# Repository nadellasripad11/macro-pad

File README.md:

# macro pad

a small macro pad i designed for week 5 freestyle. looks only, it is a
display model, it just has to look good on a desk.

## the idea

i wanted to make something clean that looks good on my desk every day.

so i started designing a macro pad with 12 keys and a scroll wheel on
the side. no screen, no rgb, no wiring, just something clean that looks
good. the look is minimal black and silver.

## what i am building

* 12 keys arranged in a 3x4 grid
* a silver metal mouse scroll wheel in a slot on the right edge, about
  half of it sticking out past the edge, like a mouse wheel
* black keycaps with little grey line icons instead of words
* a silver aluminum plate
* no board, no pcb, no wiring, no firmware, it does not work as a
  keyboard

the keycaps are relegendable, i print the line icons and slide them
under the clear tops. the switches just clip into the plate and hold
the keycaps, no soldering. the wheel is a real 25 mm mouse wheel, the
little encoder behind it only holds its axle, it is not wired to
anything.

## the hardware

the plate is custom cut aluminum, 112 by 70 mm, from md cnc. the
switches are gateron milky pro yellow, they clip into the plate and
hold the keycaps. the wheel is a metal mouse scroll wheel, about 25 mm,
for a logitech g102/g304/g305, and the encoder under it is a ttc 11 mm
mouse wheel encoder, mount only.

here are some of the main dimensions:

component	dimensions
plate	112 x 70 mm
key layout	3 x 4
key spacing	19.05 mm
key cutouts	14 x 14 mm
wheel slot	25 mm long plus clearance, width is the wheel thickness
plus about 1 mm, measure the wheel with calipers on arrival first

the dxf still has the old 7 mm round knob hole in it, the slot goes in
once the wheel is measured.

## the design files

everything is organized in the repository so the design can be reviewed
and worked on separately.

* plate/ contains the plate dxf
* images/ contains design and plate images
* cart-screenshots/ contains parts and quote screenshots

the pcb/ and firmware/ files still in this repo are from the earlier
functional plan and are not part of this build. the gerbers were not
plotted in kicad, they were generated in python, do not order from
them. there are also pin mappings, a netlist, and a draft bill of
materials from that earlier plan, also not part of this build.

## parts and costs

tier 1, total $28.77 at regular prices, verified live november 8. cap
is $33, headroom $4.23. all five lines ship free.

part	price
md cnc custom plate, aluminum, 112x70	$7.15
gateron milky pro yellow switches, 2x 10 pack	$7.22
metal mouse scroll wheel, silver, 25mm	$4.21
ttc mouse wheel encoder, 11mm	$1.61
black relegendable keycaps, 12 pack	$8.58

the plate price is quote-based, $7.15 is the lowest listed tier,
unconfirmed until md cnc quotes the dxf. the full breakdown is in
BOM-draft.md.

## current progress

this is still a design project, not a finished physical build. the
plate dxf, the look, and the parts list are in the repository.

there are a few things i still need to check before ordering anything:

* measure the wheel thickness with calipers on arrival, then cut the
  slot in the plate dxf
* get the md cnc quote from the drawing
* check the black caps stock again, only 1 left at that listing
* finalize the plate thickness, mounting holes, and corner radius

## what is next

the next step is getting the plate cut, then putting it together and
seeing how it looks on a desk.

## a little context

this was made for half life week 5 freestyle, as part of weeks 5 and 10.

it is a display model, not a working keyboard. the shape, spacing, and
finish are the whole point.

more updates once there is an actual macro pad on my desk.

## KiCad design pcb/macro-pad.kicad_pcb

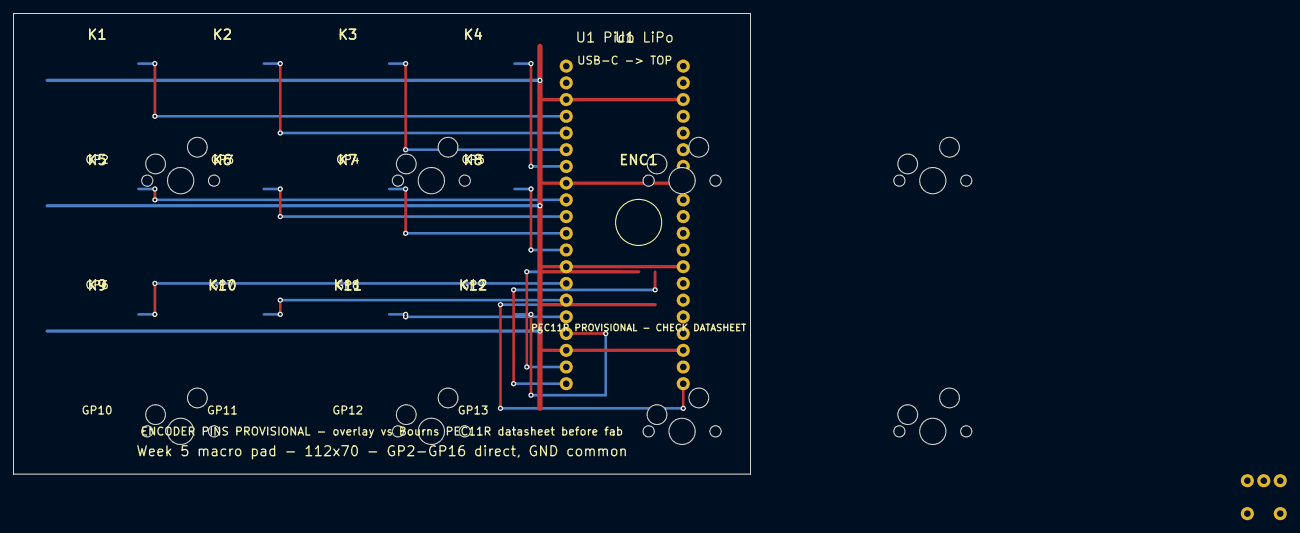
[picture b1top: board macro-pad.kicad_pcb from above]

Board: 2 copper layers, 112.0 x 70.0 mm, 14 parts (0 on the bottom side), 16 nets.

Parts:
ENC1: PEC11R-4220F-S0024
K1, K2, K3, K4, K5, K6, K7, K8, K9, K10, K11, K12: Kailh_CPG151101S11; Kailh_socket_MX
U1: Pico_LiPo_16MB; Pico_2x20

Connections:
GND: ENC1.2, ENC1.5, K1.2, K2.2, K3.2, K4.2, K5.2, K6.2, K7.2, K8.2, K9.2, K10.2, K11.2, K12.2, U1.3, U1.8, U1.13, U1.18, U1.23, U1.28, U1.33, U1.38
GP2: K1.1, U1.4
GP3: K2.1, U1.5
GP4: K3.1, U1.6
GP5: K4.1, U1.7
GP6: K5.1, U1.9
GP7: K6.1, U1.10
GP8: K7.1, U1.11
GP9: K8.1, U1.12
GP10: K9.1, U1.14
GP11: K10.1, U1.15
GP12: K11.1, U1.16
GP13: K12.1, U1.17
GP14: ENC1.1, U1.19
GP15: ENC1.3, U1.20
GP16: ENC1.4, U1.21

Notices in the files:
parts and their libraries:
Kailh CPG151101S11 hot-swap socket MX, daprice keyswitches.pretty Kailh_socket_MX CC BY-SA 4.0
